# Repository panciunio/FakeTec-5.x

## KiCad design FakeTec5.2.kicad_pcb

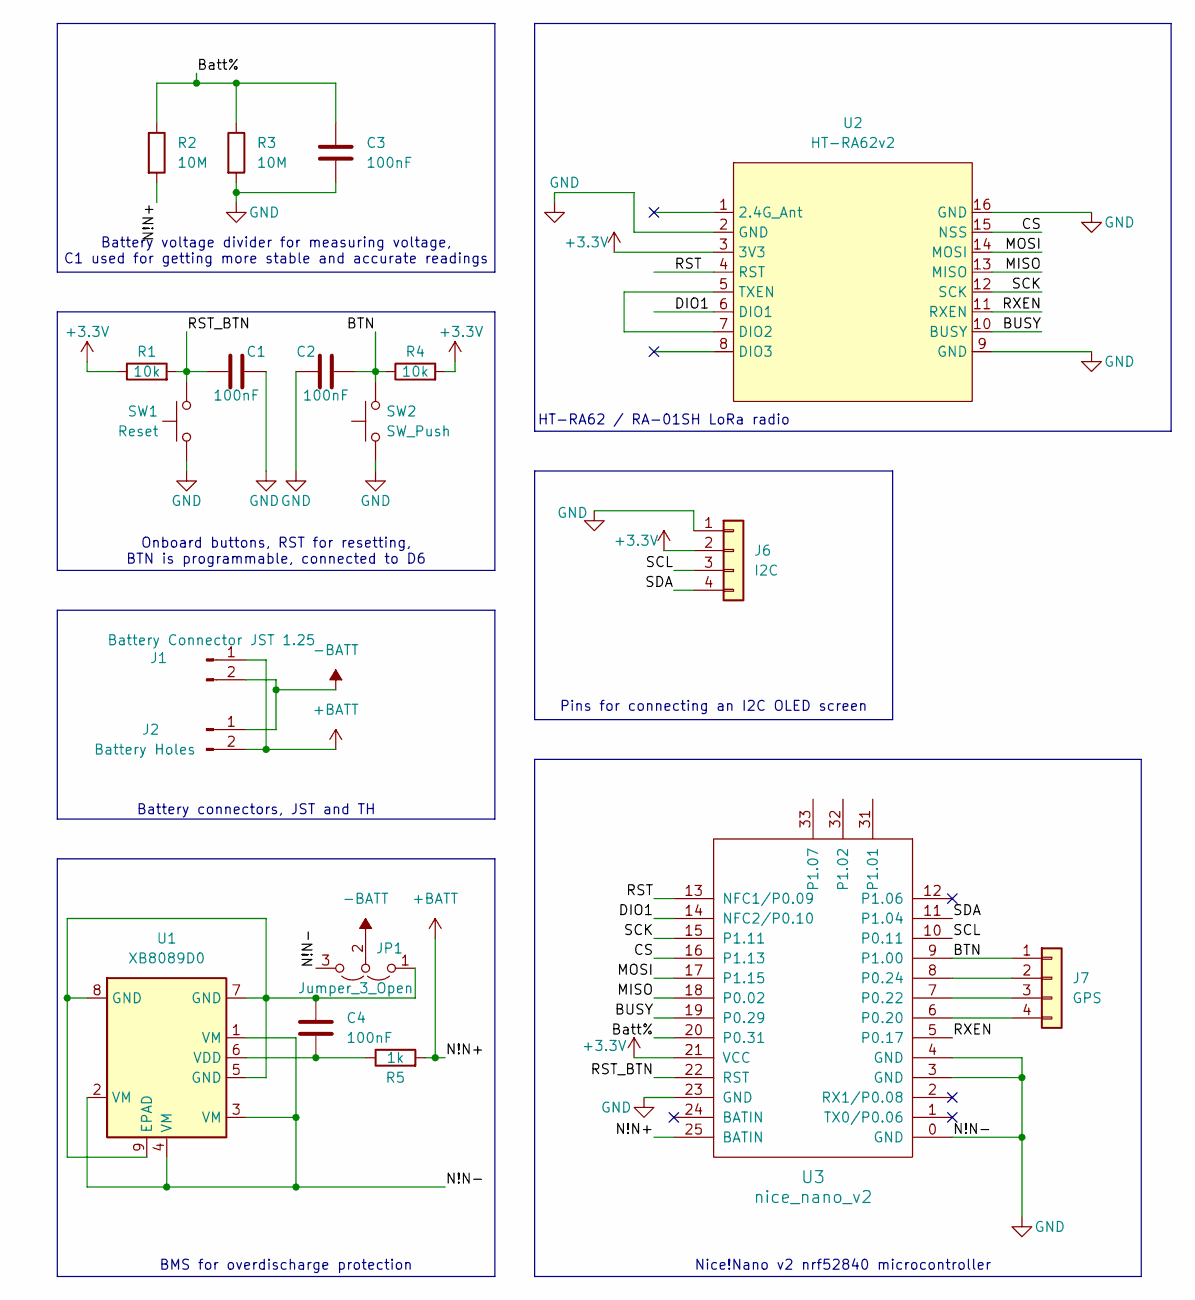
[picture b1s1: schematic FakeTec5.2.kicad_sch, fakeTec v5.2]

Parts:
C1, C2, C3, C4: 100nF; C_0805_2012Metric_Pad1.18x1.45mm_HandSolder
J1: Battery Connector JST 1.25; JST_GH_SM02B-GHS-TB_1x02-1MP_P1.25mm_Horizontal
J2: Battery Holes; PinHeader_1x02_P2.54mm_Vertical
J6: I2C; PinHeader_1x04_P2.54mm_Vertical
J7: GPS; PinHeader_1x04_P2.54mm_Vertical
JP1: Jumper_3_Open; SolderJumper-3_P1.3mm_Open_RoundedPad1.0x1.5mm
R1, R4: 10k; R_0805_2012Metric_Pad1.20x1.40mm_HandSolder
R2, R3: 10M; R_0805_2012Metric_Pad1.20x1.40mm_HandSolder
R5: 1k; R_0805_2012Metric_Pad1.20x1.40mm_HandSolder
SW1: Reset; SW_Push_SPST_NO_Alps_SKRK
SW2: SW_Push; SW_Push_SPST_NO_Alps_SKRK
U1: XB8089D0; SOIC-8-1EP_3.9x4.9mm_P1.27mm_EP2.41x3.3mm
U2: HT-RA62v2; HT-RA62-LoRa
U3: nice_nano_v2

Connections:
+3.3V: J6.2, R1.1, R4.2, U2.3 (3V3), U3.21 (VCC)
+BATT: J1.1, J2.2, R2.2, R5.2, U3.25 (BATIN)
-BATT: J1.2, J2.1, JP1.2 (C)
/BTN: C2.2, J7.1, R4.1, SW2.2, U3.9 (P1.00)
/BUSY: U2.10 (BUSY), U3.19 (P0.29)
/Batt%: C3.1, R2.1, R3.1, U3.20 (P0.31)
/CS: U2.15 (NSS), U3.16 (P1.13)
/DIO1: U2.6 (DIO1), U3.14 (NFC2/P0.10)
/MISO: U2.13 (MISO), U3.18 (P0.02)
/MOSI: U2.14 (MOSI), U3.17 (P1.15)
/RST: U2.4 (RST), U3.13 (NFC1/P0.09)
/RST_BTN: C1.1, R1.2, SW1.2, U3.22 (RST)
/RXEN: U2.11 (RXEN), U3.5 (P0.17)
/SCK: U2.12 (SCK), U3.15 (P1.11)
/SCL: J6.3, U3.10 (P0.11)
/SDA: J6.4, U3.11 (P1.04)
GND: C1.2, C2.1, C3.2, J6.1, JP1.3 (B), R3.2, SW1.1, SW2.1, U1.1 (VM), U1.2 (VM), U1.3 (VM), U1.4 (VM), U2.2 (GND), U2.9 (GND), U2.16 (GND), U3.0 (GND), U3.3 (GND), U3.4 (GND), U3.23 (GND)
unnamed: J7.2, U3.8 (P0.24)
unnamed: J7.3, U3.7 (P0.22)
unnamed: J7.4, U3.6 (P0.20)
unnamed: C4.1, JP1.1 (A), U1.5 (GND), U1.7 (GND), U1.8 (GND), U1.9 (EPAD)
unnamed: C4.2, R5.1, U1.6 (VDD)
unnamed: U2.5 (TXEN), U2.7 (DIO2)

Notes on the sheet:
Nice!Nano v2 nrf52840 microcontroller
BMS for overdischarge protection
Battery voltage divider for measuring voltage, C1 used for getting more stable and accurate readings
HT-RA62 / RA-01SH LoRa radio
Onboard buttons, RST for resetting, BTN is programmable, connected to D6
Battery connectors, JST and TH
Pins for connecting an I2C OLED screen

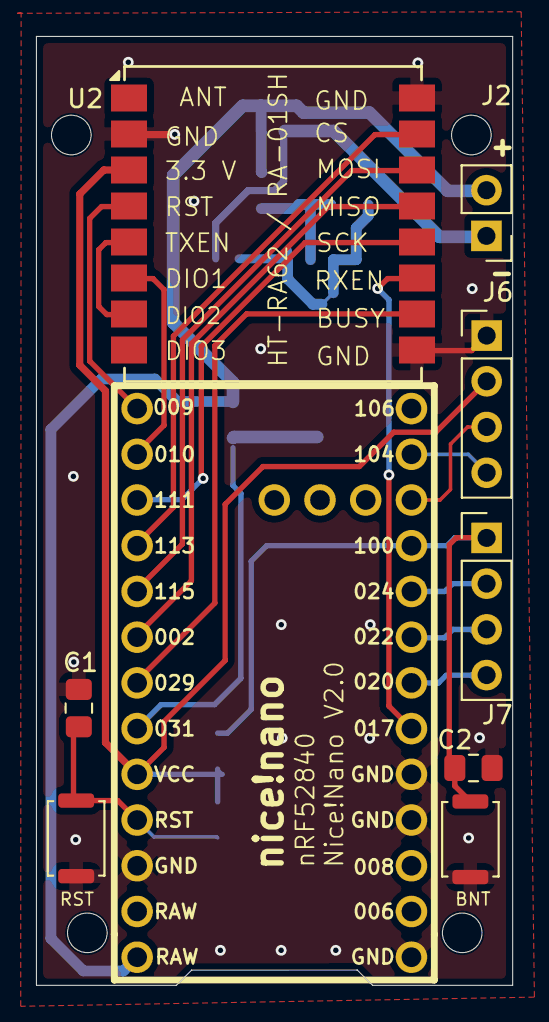
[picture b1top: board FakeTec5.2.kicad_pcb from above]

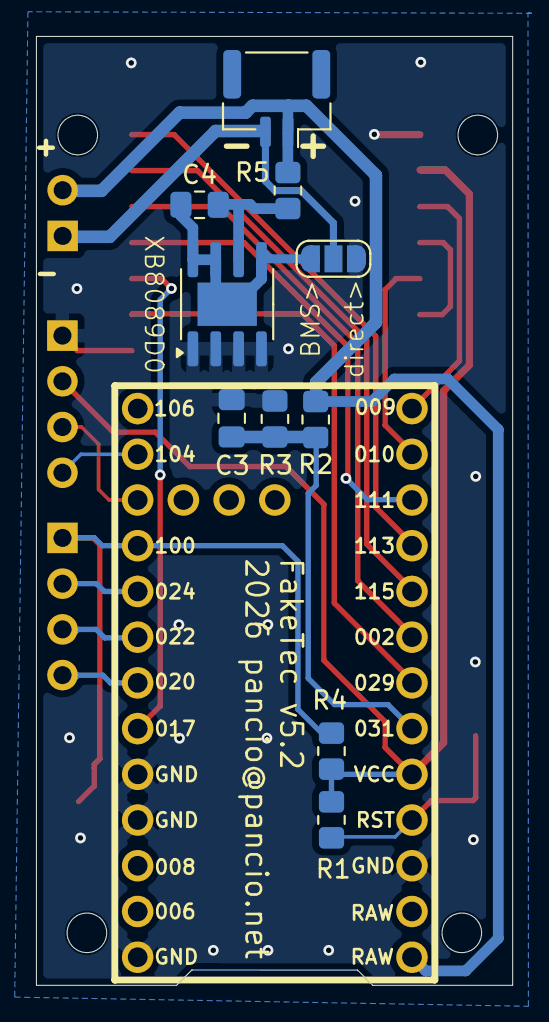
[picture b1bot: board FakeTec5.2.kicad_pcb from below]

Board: 2 copper layers, 26.5 x 52.7 mm, 19 parts (10 on the bottom side), 23 nets.
